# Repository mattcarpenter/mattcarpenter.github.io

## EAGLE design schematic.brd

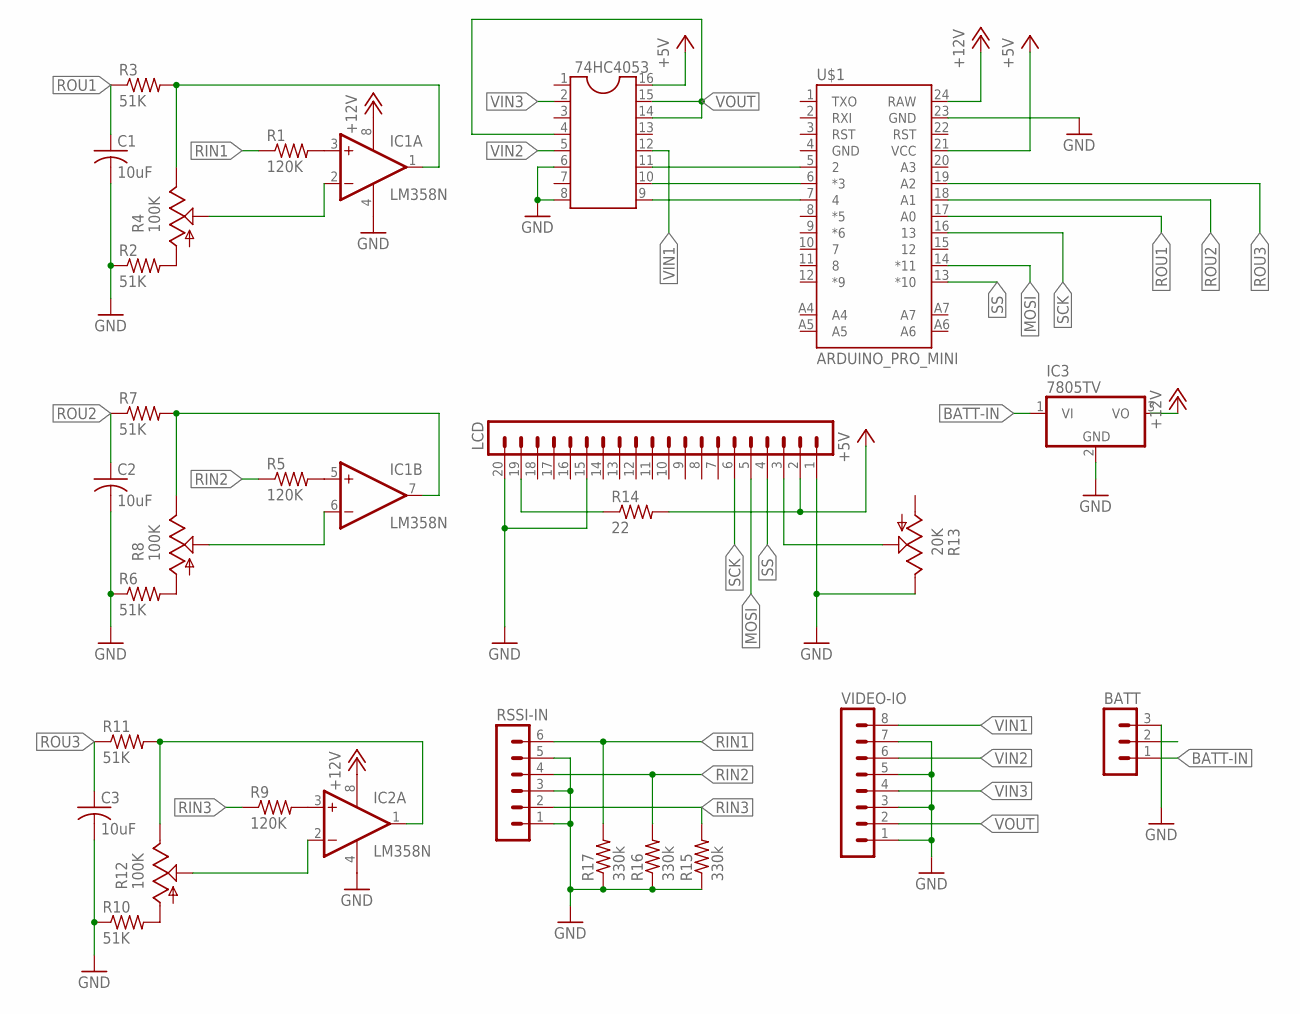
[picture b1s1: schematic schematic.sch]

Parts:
74HC4053: DIL16
BATT: MA03-1
C1, C2, C3: 10uF; C025-025X050
IC1, IC2: LM358N; DIL08
IC3: 7805TV; TO220V
LCD: MA20-1L
R1, R5, R9: 120K; 0207/10
R2, R3, R6, R7, R10, R11: 51K; 0207/10
R4, R8, R12: 100K; S64W
R13: 20K; S64W
R14: 22; 0207/10
R15, R16, R17: 330k; 0207/10
RSSI-IN: MA06-1
U$1: ARDUINO_PRO_MINI
VIDEO-IO: MA08-1

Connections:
+5V: 74HC4053.16, LCD.2, R14.2, U$1.21 (VCC)
+12V: IC1.8 (V+), IC2.8 (V+), IC3.3 (VO), U$1.24 (RAW)
BATT-IN: BATT.1, IC3.1 (VI)
GND: 74HC4053.6, 74HC4053.8, BATT.3, C1.2, C2.2, C3.2, IC1.4 (V-), IC2.4 (V-), IC3.2 (GND), LCD.1, LCD.15, LCD.20, R2.1, R6.1, R10.1, R13.E, R15.1, R16.1, R17.1, RSSI-IN.1, RSSI-IN.3, RSSI-IN.5, U$1.23 (GND), VIDEO-IO.1, VIDEO-IO.3, VIDEO-IO.5, VIDEO-IO.7
MOSI: LCD.5, U$1.14 (*11)
unnamed: 74HC4053.11, U$1.5 (2)
unnamed: 74HC4053.10, U$1.6 (*3)
unnamed: 74HC4053.9, U$1.7 (4)
unnamed: IC1.3 (+IN), R1.2
unnamed: IC1.1 (OUT), R3.2, R4.E
unnamed: IC1.2 (-IN), R4.S
unnamed: R2.2, R4.A
unnamed: IC1.7 (OUT), R7.2, R8.E
unnamed: R6.2, R8.A
unnamed: IC1.6 (-IN), R8.S
unnamed: IC2.1 (OUT), R11.2, R12.E
unnamed: R10.2, R12.A
unnamed: IC2.2 (-IN), R12.S
unnamed: IC1.5 (+IN), R5.2
unnamed: IC2.3 (+IN), R9.2
unnamed: LCD.3, R13.S
unnamed: LCD.19, R14.1
RIN1: R1.1, R17.2, RSSI-IN.6
RIN2: R5.1, R16.2, RSSI-IN.4
RIN3: R9.1, R15.2, RSSI-IN.2
ROU1: C1.1, R3.1, U$1.17 (A0)
ROU2: C2.1, R7.1, U$1.18 (A1)
ROU3: C3.1, R11.1, U$1.19 (A2)
SCK: LCD.6, U$1.16 (13)
SS: LCD.4, U$1.13 (*10)
VIN1: 74HC4053.12, VIDEO-IO.8
VIN2: 74HC4053.5, VIDEO-IO.6
VIN3: 74HC4053.2, VIDEO-IO.4
VOUT: 74HC4053.4, 74HC4053.14, 74HC4053.15, VIDEO-IO.2

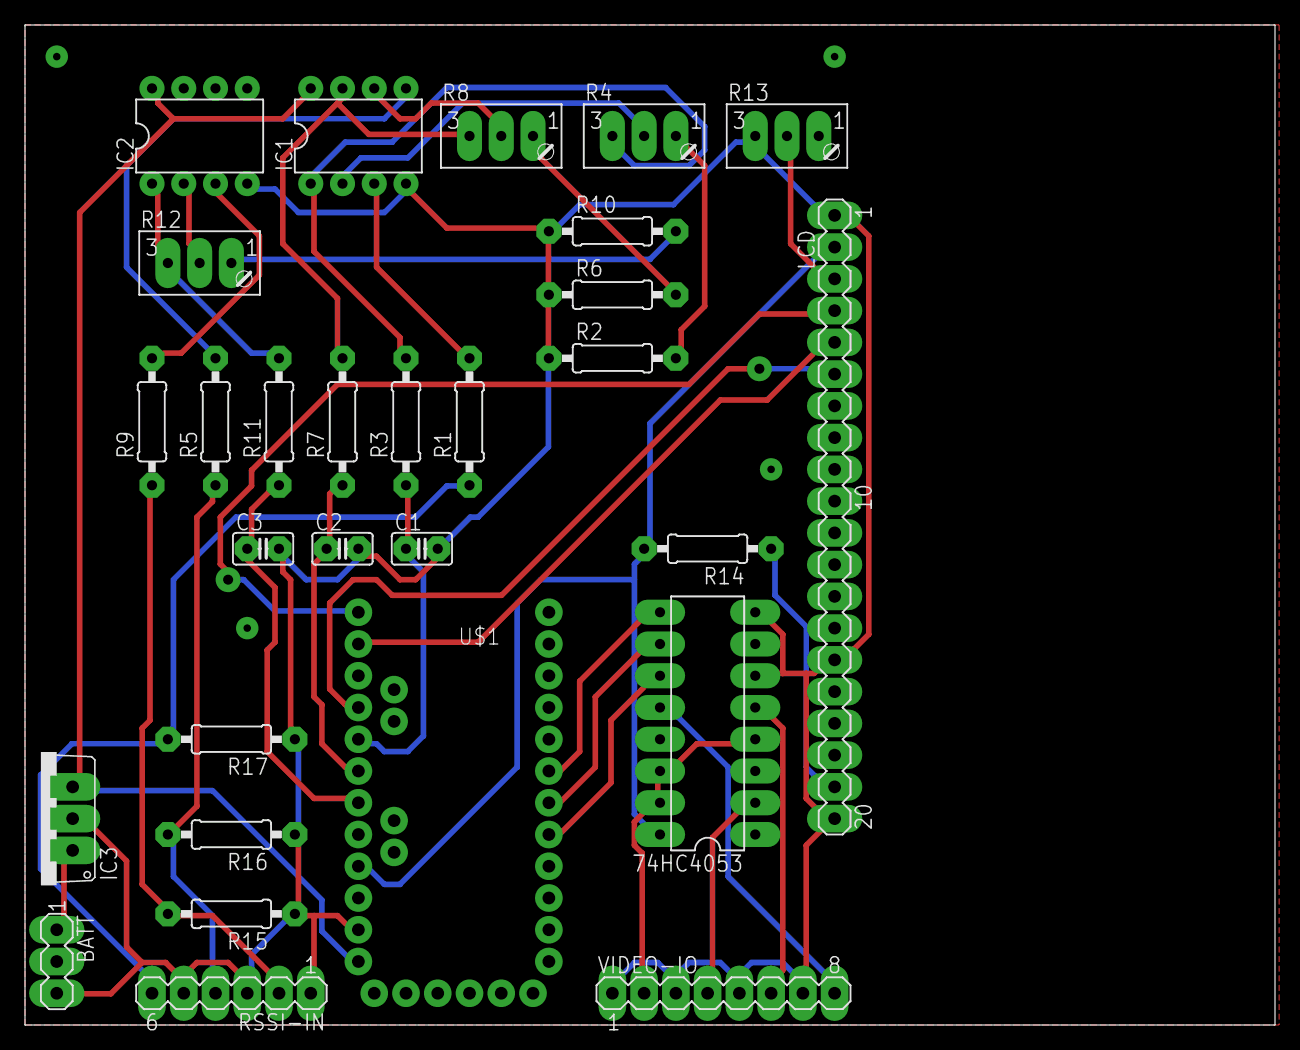
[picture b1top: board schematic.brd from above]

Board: 2 copper layers, 100.0 x 80.0 mm, 29 parts (0 on the bottom side), 34 nets.

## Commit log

2015-03-01 added some images
2015-03-01 added small images
2015-03-01 added small schematic and board

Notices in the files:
parts and their libraries:
SparkFun-Boards: Licensing: Creative Commons ShareAlike 4.0 International - https://creativecommons.org/licenses/by-sa/4.0
